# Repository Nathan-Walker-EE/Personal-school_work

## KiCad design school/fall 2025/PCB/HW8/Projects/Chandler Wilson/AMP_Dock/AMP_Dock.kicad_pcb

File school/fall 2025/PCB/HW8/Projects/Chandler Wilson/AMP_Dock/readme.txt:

Title: AMP Dock
REV: 1.0-A

Description:
The AMP Dock is a power conversion circuit that consists of two 
different buck converters that take battery inputs from a Milwaukee M18 
and a DeWalt XR. 
The system steps the voltage of these batteries down to feed a 12 V bus 
that is used to output 12 V to power a fish finder device or other similar 12 V 
powered device. The 12 V bus is also parallelly connected to a separate buck 
converter that steps down to 5V for USB-A and USB-C outputs for phone charging. 
This device will be contained in a IP67 container that has mounting points for 
the batteries and USB output ports.

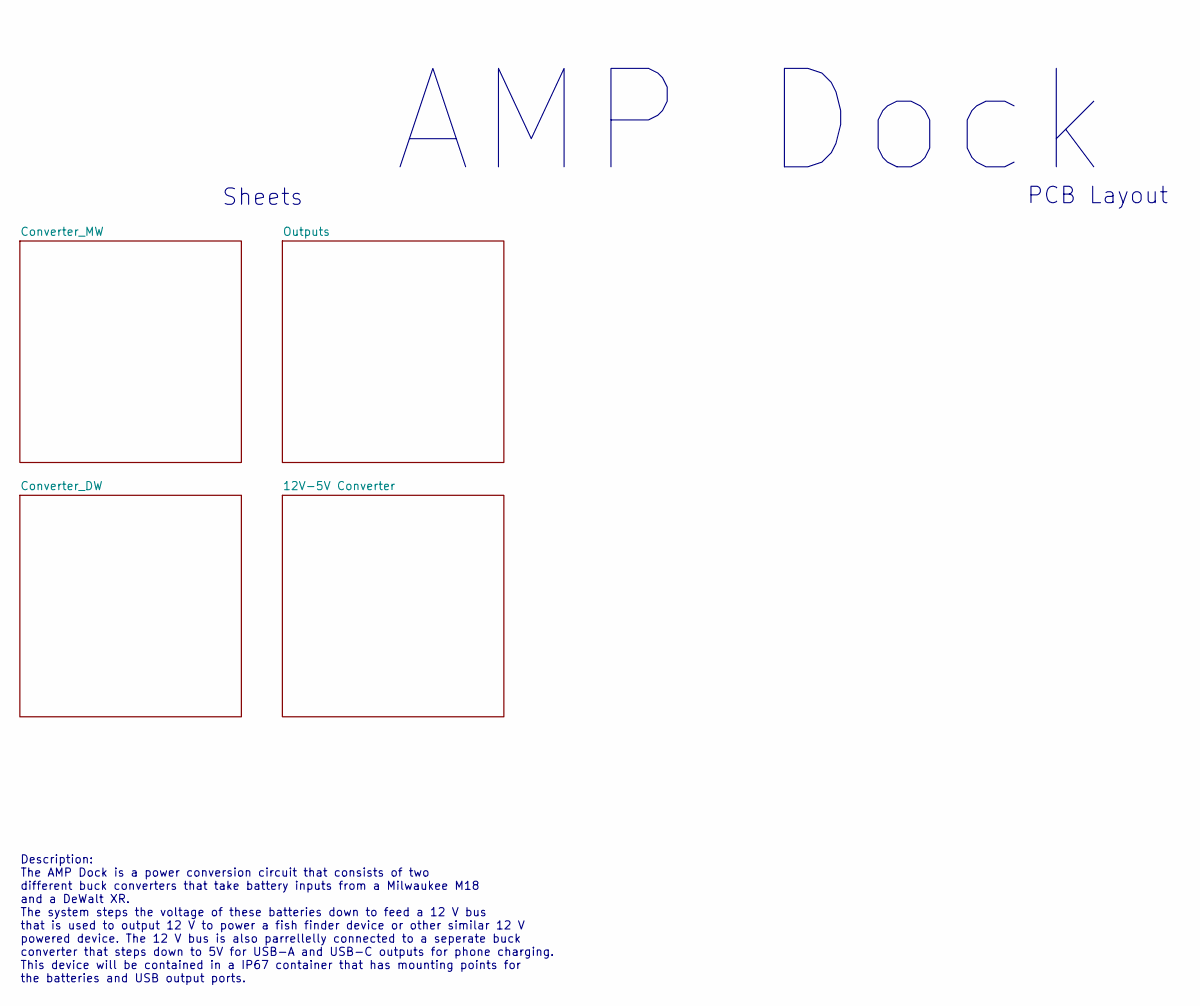
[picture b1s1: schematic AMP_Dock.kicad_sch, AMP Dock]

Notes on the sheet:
AMP Dock
Sheets
Description: The AMP Dock is a power conversion circuit that consists of two different buck converters that take battery inputs from a Milwaukee M18 and a DeWalt XR. The system steps the voltage of these batteries down to feed a 12 V bus that is used to output 12 V to power a fish finder device or 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
PCB Layout

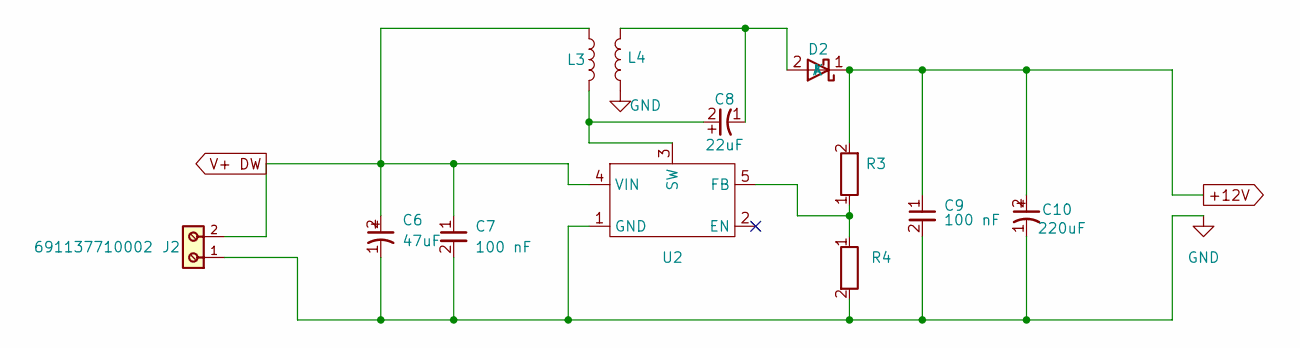
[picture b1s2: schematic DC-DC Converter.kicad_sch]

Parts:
C6: 47uF; CAP_EEFK_D_PAN
C7, C9: 100 nF; C_0805_2012Metric
C8: 22uF; CAP_6.3 X 5.8_PAN
C10: 220uF; CAP_EEFK_F_PAN
D2: DIOM7959X262N
J2: 691137710002
L3, L4: SRR1280-330M; IND_BOURNS_SRR1280
R3: R_0402_1005Metric
R4: R_0603_1608Metric
U2: XL6019

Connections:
+12V: C9.1, C10.2, D2.1 (K), R3.2; also elsewhere on the board
GND: C6.1, C7.2, C9.2, C10.1, J2.1, L4.1, R4.2, U2.1 (GND); also elsewhere on the board
unnamed: C8.1, D2.2 (A), L4.2
unnamed: R3.1, R4.1, U2.5 (FB)
unnamed: C8.2, L3.2, U2.3 (SW)
V+ DW: C6.2, C7.1, J2.2, L3.1, U2.4 (VIN)

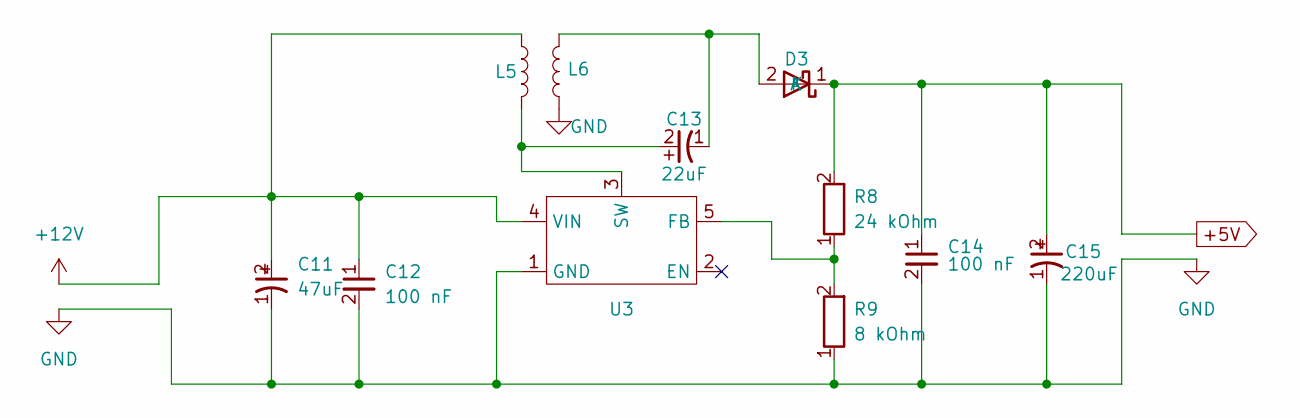
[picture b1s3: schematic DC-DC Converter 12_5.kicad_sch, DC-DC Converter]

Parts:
C11: 47uF; CAP_EEFK_D_PAN
C12, C14: 100 nF; C_0805_2012Metric
C13: 22uF; CAP_6.3 X 5.8_PAN
C15: 220uF; CAP_EEFK_F_PAN
D3: DIOM7959X262N
L5, L6: SRR1280-330M; IND_BOURNS_SRR1280
R8: 24 kOhm; R_0805_2012Metric
R9: 8 kOhm; R_0603_1608Metric
U3: XL6019

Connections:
+5V: C14.1, C15.2, D3.1 (K), R8.2; also elsewhere on the board
+12V: C11.2, C12.1, L5.1, U3.4 (VIN); also elsewhere on the board
GND: C11.1, C12.2, C14.2, C15.1, L6.1, R9.1, U3.1 (GND); also elsewhere on the board
unnamed: C13.1, D3.2 (A), L6.2
unnamed: R8.1, R9.2, U3.5 (FB)
unnamed: C13.2, L5.2, U3.3 (SW)

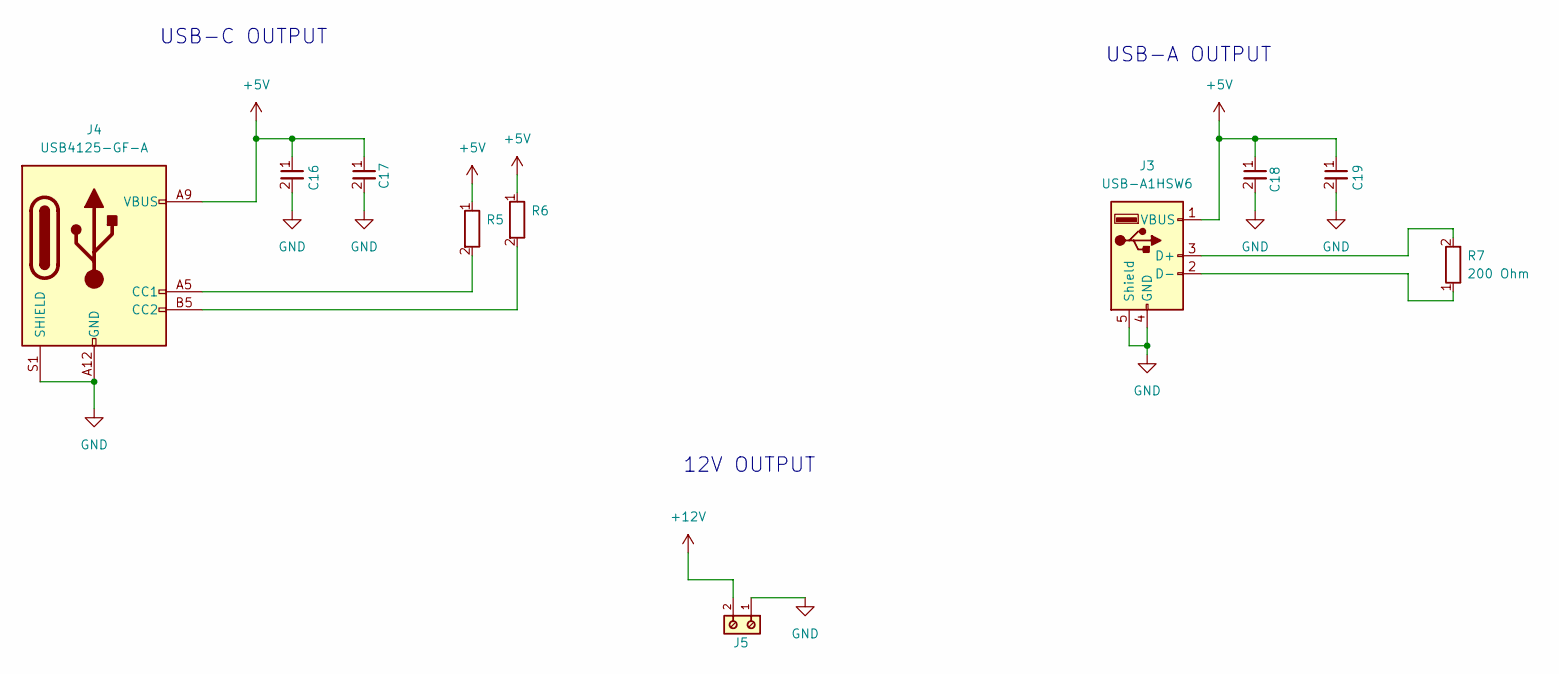
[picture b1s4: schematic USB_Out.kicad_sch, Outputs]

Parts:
C16, C17, C18, C19: 100 nF; C_0805_2012Metric
J3: USB-A1HSW6; OST_USB-A1HSW6
J4: USB4125-GF-A; GCT_USB4125-GF-A_REVA2
J5: 691137710002
R5, R6: R_0805_2012Metric
R7: 200 Ohm; R_0805_2012Metric

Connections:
+5V: C16.1, C17.1, C18.1, C19.1, J3.1 (VBUS), J4.A9 (VBUS), J4.B9 (VBUS), R5.1, R6.1; also elsewhere on the board
+12V: J5.2; also elsewhere on the board
GND: C16.2, C17.2, C18.2, C19.2, J3.4 (GND), J3.5 (Shield), J4.A12 (GND), J4.B12 (GND), J4.S1 (SHIELD), J5.1; also elsewhere on the board
unnamed: J3.3 (D+), R7.2
unnamed: J3.2 (D-), R7.1
unnamed: J4.A5 (CC1), R5.2
unnamed: J4.B5 (CC2), R6.2

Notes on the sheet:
12V OUTPUT
USB-C OUTPUT
USB-A OUTPUT

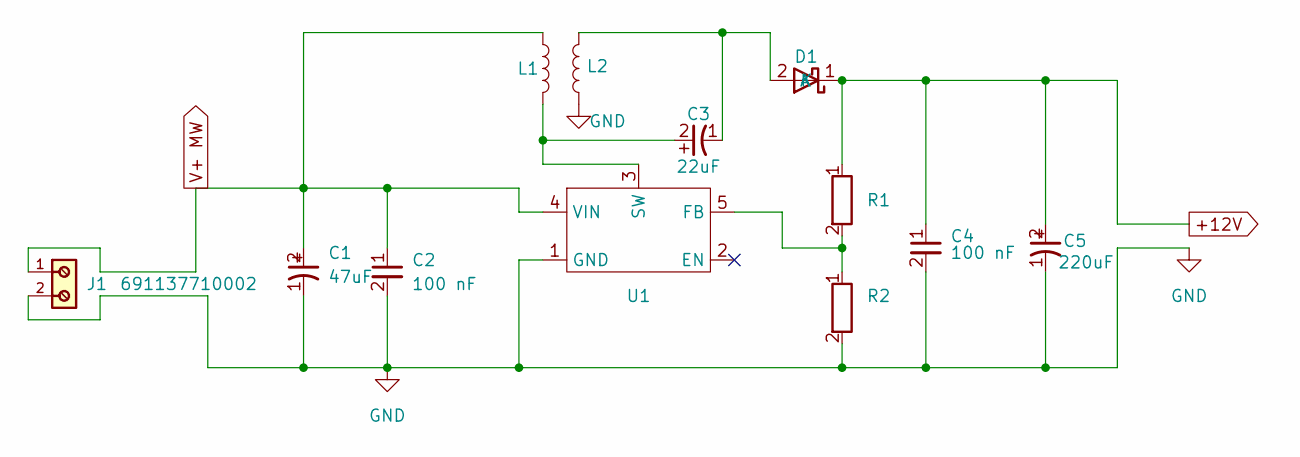
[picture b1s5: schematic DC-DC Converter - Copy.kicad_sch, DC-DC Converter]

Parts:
C1: 47uF; CAP_EEFK_D_PAN
C2, C4: 100 nF; C_0805_2012Metric
C3: 22uF; CAP_6.3 X 5.8_PAN
C5: 220uF; CAP_EEFK_F_PAN
D1: DIOM7959X262N
J1: 691137710002
L1, L2: SRR1280-330M; IND_BOURNS_SRR1280
R1: 24 kohm; R_0402_1005Metric
R2: R_0603_1608Metric
U1: XL6019

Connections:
+12V: C4.1, C5.2, D1.1 (K), R1.1; also elsewhere on the board
GND: C1.1, C2.2, C4.2, C5.1, J1.2, L2.1, R2.2, U1.1 (GND); also elsewhere on the board
unnamed: C3.1, D1.2 (A), L2.2
unnamed: R1.2, R2.1, U1.5 (FB)
unnamed: C3.2, L1.2, U1.3 (SW)
V+ MW: C1.2, C2.1, J1.1, L1.1, U1.4 (VIN)

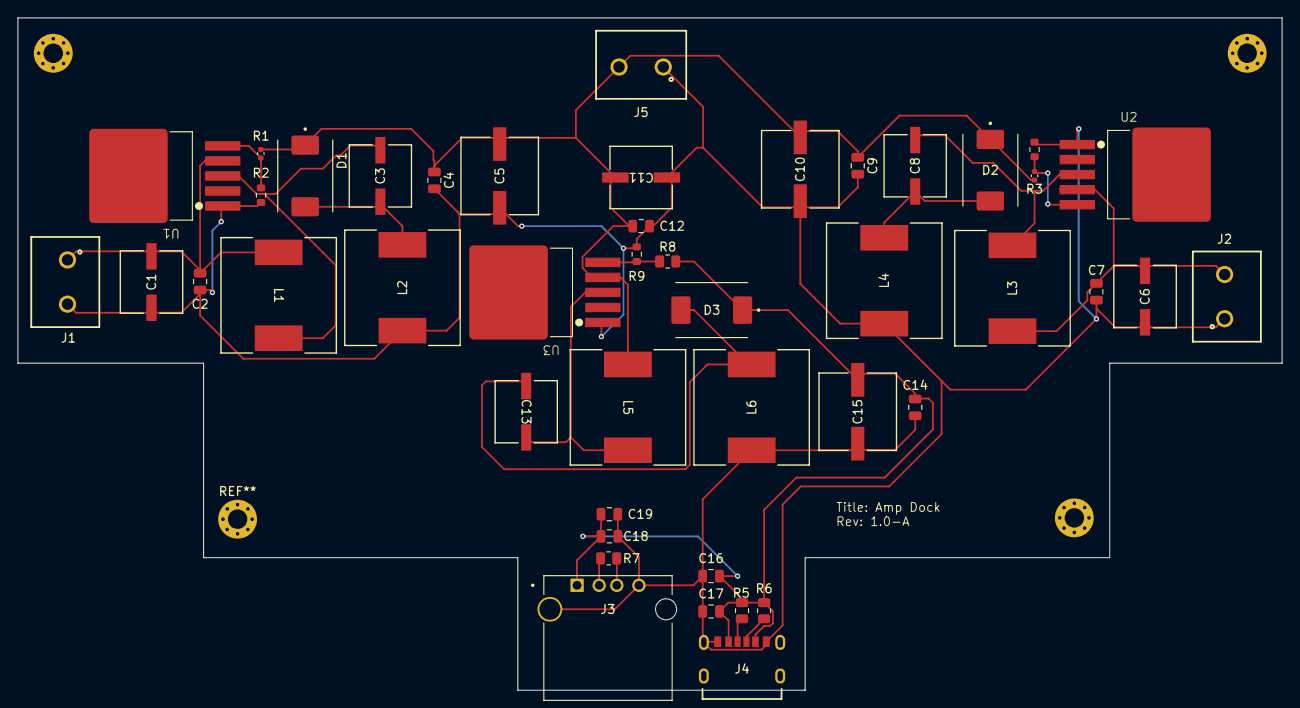
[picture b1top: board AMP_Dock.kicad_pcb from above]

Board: 2 copper layers, 143.0 x 76.1 mm, 45 parts (0 on the bottom side), 18 nets.

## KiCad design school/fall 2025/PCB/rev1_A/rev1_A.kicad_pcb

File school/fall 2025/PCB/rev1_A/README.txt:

This is Rev1_A of my PCB. It's intended purpose is to be a pmod kit
for the Basys 3 board.

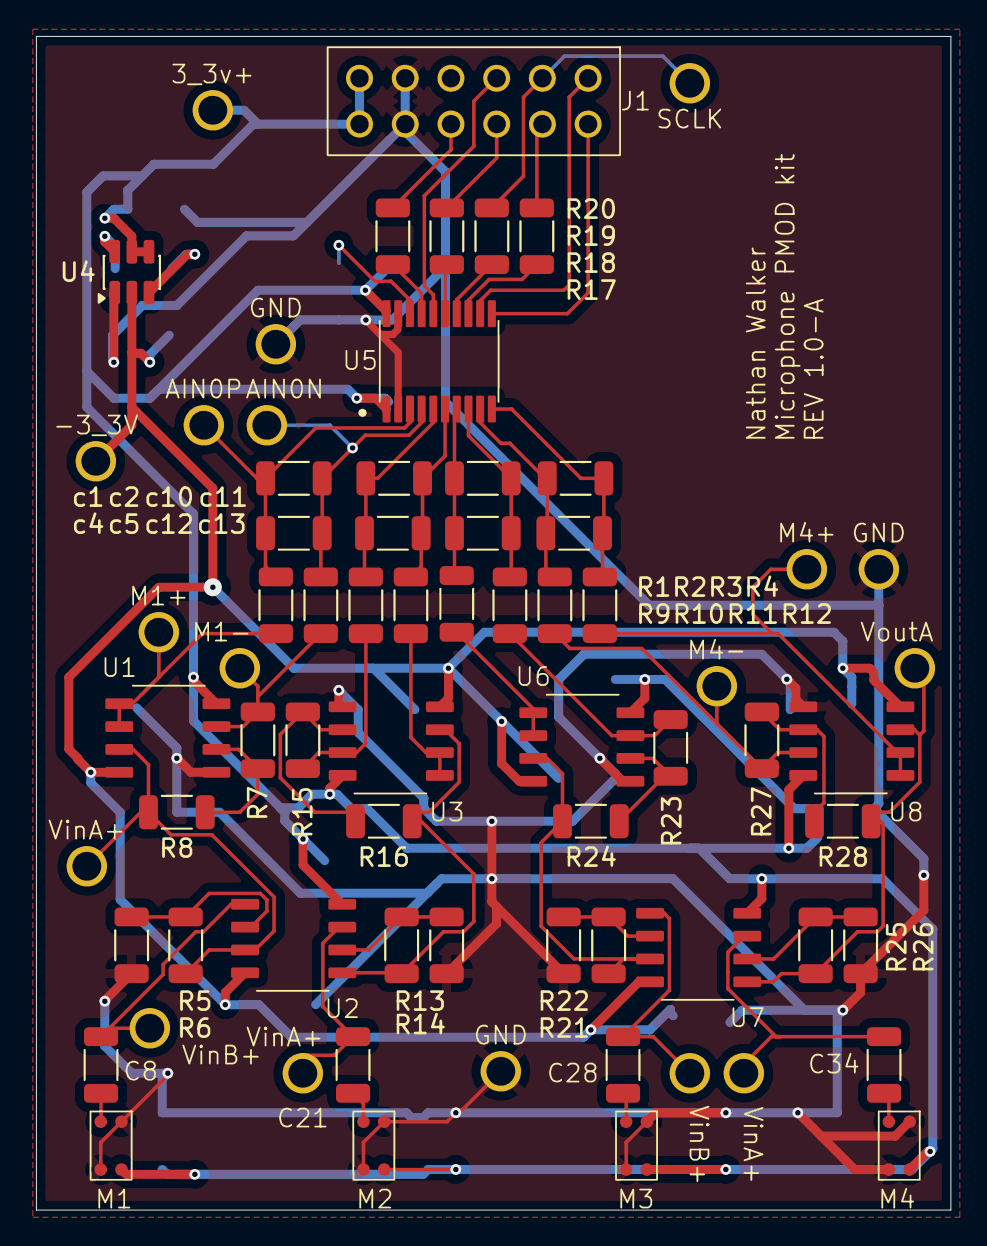
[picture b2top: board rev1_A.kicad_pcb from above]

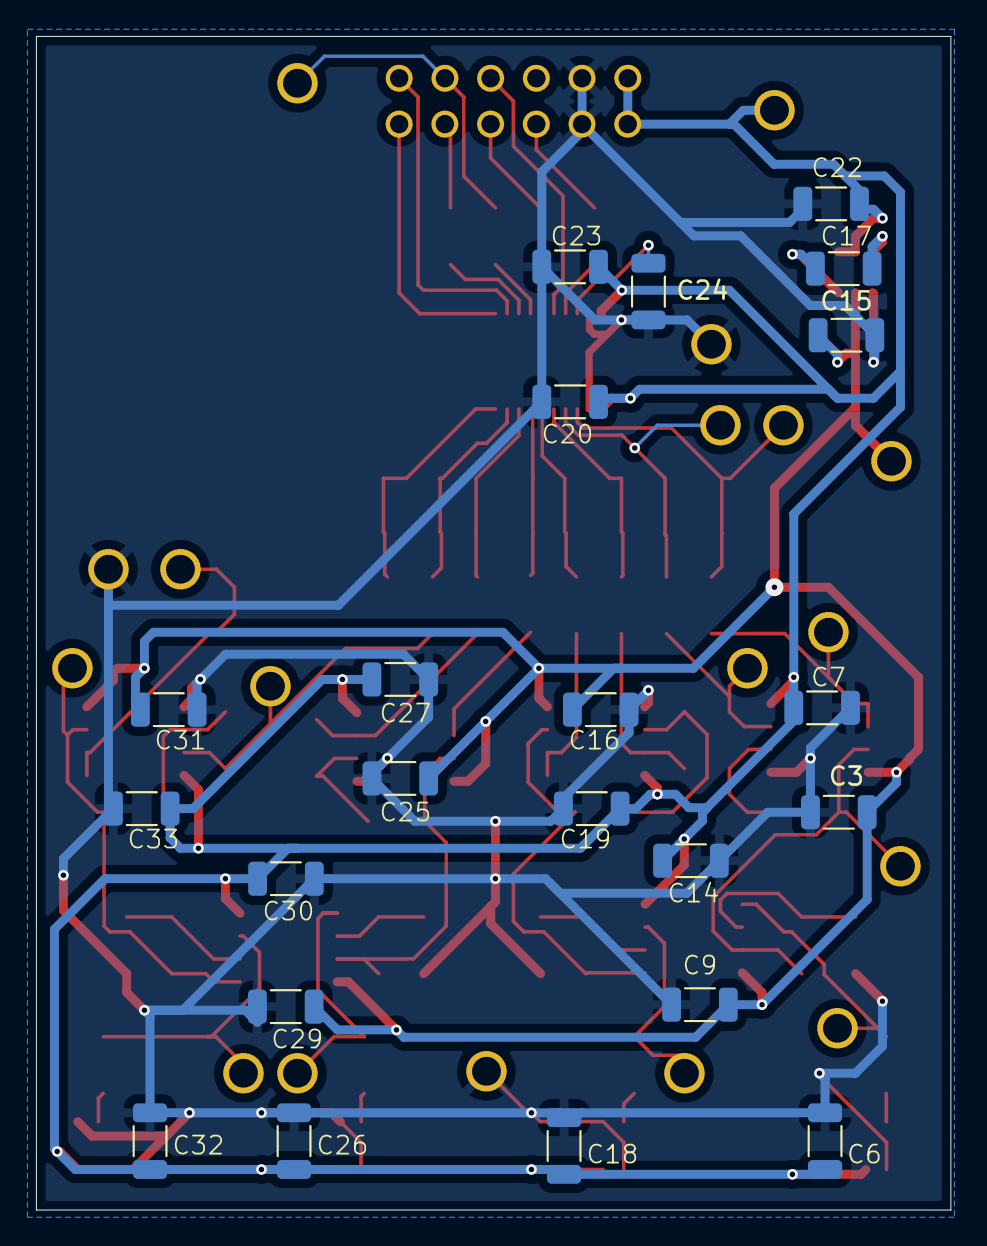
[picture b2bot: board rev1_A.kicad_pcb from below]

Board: 2 copper layers, 50.8 x 65.2 mm, 93 parts (22 on the bottom side), 53 nets.

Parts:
3_3v+: 5010
-3_3V: 5010
AIN0N, AIN0P: 5010
C3, C6, C7, C9, C14, C16, C17, C18, C19, C20, C22, C23, C25, C26, C27, C29, C30, C31, C32, C33: 1 uF; 1206 capacitor
C8, C21, C28, C34: 0.1 uF; 1206 capacitor
C15: 2.2 uF; L_1206_3216Metric
C24: 220nF; L_1206_3216Metric
GND: 5010
GND#2, GND#3: 5010
J1: PHED-RS006G1ABOGA-C006
M1, M2, M3, M4: 3SM123C4T1QA
M1+, M1-, M4+, M4-: 5010
R1, R2, R3, R4, R9, R10, R11, R12: 300; L_1206_3216Metric
R5, R14, R21, R26: 249k; L_1206_3216Metric
R6, R7, R8, R13, R15, R16, R22, R23, R24, R25, R27, R28: 10k; L_1206_3216Metric
R17, R18, R19, R20: 47; L_1206_3216Metric
SCLK: 5010
U1, U2, U3, U6, U7, U8: MCP6002
U4: SOT-23-6
U5: ADS130B02-Q1
VinA+: 5010
VinA+#2, VinA+#3: 5010
VinB+: 5010
VinB+#2: 5010
VoutA: 5010
c1, c2, c4, c5, c10, c11, c12, c13: 10nf; L_1206_3216Metric

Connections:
/3_3V+: 3_3v+.1, C6.1, C7.2, C14.1, C18.1, C19.2, C20.1, C22.1, C23.1, C26.1, C27.2, C30.1, C32.1, C33.2, J1.6 (JB6), J1.12 (JB12), M1.1 (VDD), M2.1 (VDD), M3.1 (VDD), M4.1 (VDD), U1.8 (VDD), U2.4 (VSS), U3.8 (VDD), U4.4 (SD), U4.5 (V+), U5.1 (AVDD), U5.20 (DVDD), U6.8 (VDD), U7.4 (VSS), U8.8 (VDD)
/-3_3V: -3_3V.1, C3.1, C9.2, C15.1, C16.1, C25.1, C29.2, C31.1, U1.4 (VSS), U2.8 (VDD), U3.4 (VSS), U4.2 (OUT), U6.4 (VSS), U7.8 (VDD), U8.4 (VSS)
/AIN0N: AIN0N.1, R2.1, U5.4 (AIN0N), c1.2, c4.2
/AIN0P: AIN0P.1, R1.2, U5.3 (AIN0P), c1.1, c4.1
/AIN1N: R4.1, U5.5 (AIN1N), c2.2, c5.2
/AIN1P: R3.2, U5.6 (AIN1P), c2.1, c5.1
/AIN2N: R10.1, U5.8 (AIN2N), c10.2, c12.2
/AIN2P: R9.2, U5.7 (AIN2P), c10.1, c12.1
/AIN3N: R12.1, U5.9 (AIN3N), c11.2, c13.2
/AIN3P: R11.2, U5.10 (AIN3P), c11.1, c13.1
/CLKIN: J1.4 (JB4), R17.2
/CS_: J1.7 (JB7), U5.12 (CS_)
/DIN: J1.9 (JB9), U5.16 (DIN)
/DOUT: J1.3 (JB3), R18.2
/DRDY_: J1.2 (JB2), R20.2
/M1+: M1+.1, R1.1, U1.1 (VoutA), U1.2 (VinA-)
/M1-: M1-.1, R2.2, R7.2, U1.7 (VoutB)
/M1_amplified: R6.2, R8.1, U1.3 (VinA+), U2.7 (VoutB)
/M2+: R3.1, U3.1 (VoutA), U3.2 (VinA-)
/M2-: R4.2, R15.2, U3.7 (VoutB)
/M2_amplified: R13.2, R16.2, U2.1 (VoutA), U3.3 (VinA+)
/M3+: R9.1, U6.1 (VoutA), U6.2 (VinA-)
/M3-: R10.2, R23.2, U6.7 (VoutB)
/M3_amplified: R22.2, R24.1, U6.3 (VinA+), U7.7 (VoutB)
/M4+: M4+.1, R11.1, U8.1 (VoutA), U8.2 (VinA-)
/M4-: M4-.1, R12.2, R27.2, U8.7 (VoutB)
/M4_amplified: R25.2, R28.2, U7.1 (VoutA), U8.3 (VinA+)
/SCLK: J1.8 (JB8), R19.2, SCLK.1
/SYNC_: J1.1 (JB1), U5.11 (SYNC_)
/VinA+_M2: C21.2, U2.3 (VinA+)
/VinA+_M4: C34.2, U7.3 (VinA+)
/VinB+_M1: C8.2, U2.5 (VinB+)
/VinB+_M3: C28.2, U7.5 (VinB+)
GND: C3.2, C6.2, C7.1, C9.1, C14.2, C15.2, C16.2, C18.2, C19.1, C20.2, C22.2, C23.2, C24.2, C25.2, C26.2, C27.1, C29.1, C30.2, C31.2, C32.2, C33.1, GND.1, GND#2.1, GND#3.1, J1.5 (JB5), J1.11 (JB11), M1.2 (GND), M1.3 (GND), M2.2 (GND), M2.3 (GND), M3.2 (GND), M3.3 (GND), M4.2 (GND), M4.3 (GND), R5.2, R14.1, R21.2, R26.1, U1.5 (VinB+), U3.5 (VinB+), U4.1 (GND), U5.2 (AGND), U5.19 (DGND), U6.5 (VinB+), U8.5 (VinB+)
unnamed: C8.1, M1.4 (OUT)
unnamed: C21.1, M2.4 (OUT)
unnamed: C28.1, M3.4 (OUT)
unnamed: C34.1, M4.4 (OUT)
unnamed: R7.1, R8.2, U1.6 (VinB-)
unnamed: R13.1, R14.2, U2.2 (VinA-)
unnamed: R5.1, R6.1, U2.6 (VinB-)
unnamed: R15.1, R16.1, U3.6 (VinB-)
unnamed: C17.2, U4.6 (CAP+)
unnamed: C17.1, U4.3 (CAP-)
unnamed: C24.1, U5.18 (CAP)
unnamed: R17.1, U5.17 (CLKIN)
unnamed: R18.1, U5.15 (DOUT)
unnamed: R20.1, U5.13 (DRDY_)
unnamed: R19.1, U5.14 (SCLK)
unnamed: R23.1, R24.2, U6.6 (VinB-)
unnamed: R25.1, R26.2, U7.2 (VinA-)
unnamed: R21.1, R22.1, U7.6 (VinB-)
unnamed: R27.1, R28.1, U8.6 (VinB-)

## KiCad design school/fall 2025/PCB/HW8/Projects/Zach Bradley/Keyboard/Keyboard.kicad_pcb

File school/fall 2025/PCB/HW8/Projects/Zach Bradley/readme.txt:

Intention: Build a Split Keyboard PCB
The circuit uses switches, diodes, resistors, capacitors, MCUs, and a crystal oscillator.
The project is not quite complete, and needs a second revision to work, details below.
Another intention is to learn KiCad to progress in PCB design.

Scope: This board scans a keyboard matrix and properly relays the correct switch pressed to the PC.
The scope of this project is to anyone who needs a split keyboard for carpal tunnel protection, PCB design experience, or customization of a keyboard/PCB.

Function: Demonstrates an understanding of KiCad software and preventative measures for carpal tunnel.

IGNORED ERRORS:
None in the ERC.

Errors in the PCB include not finished routing all the necessary traces.
I have to think through the design just a bit more to ensure that I can properly separate the two sides, program the MCU properly, and route all the traces.

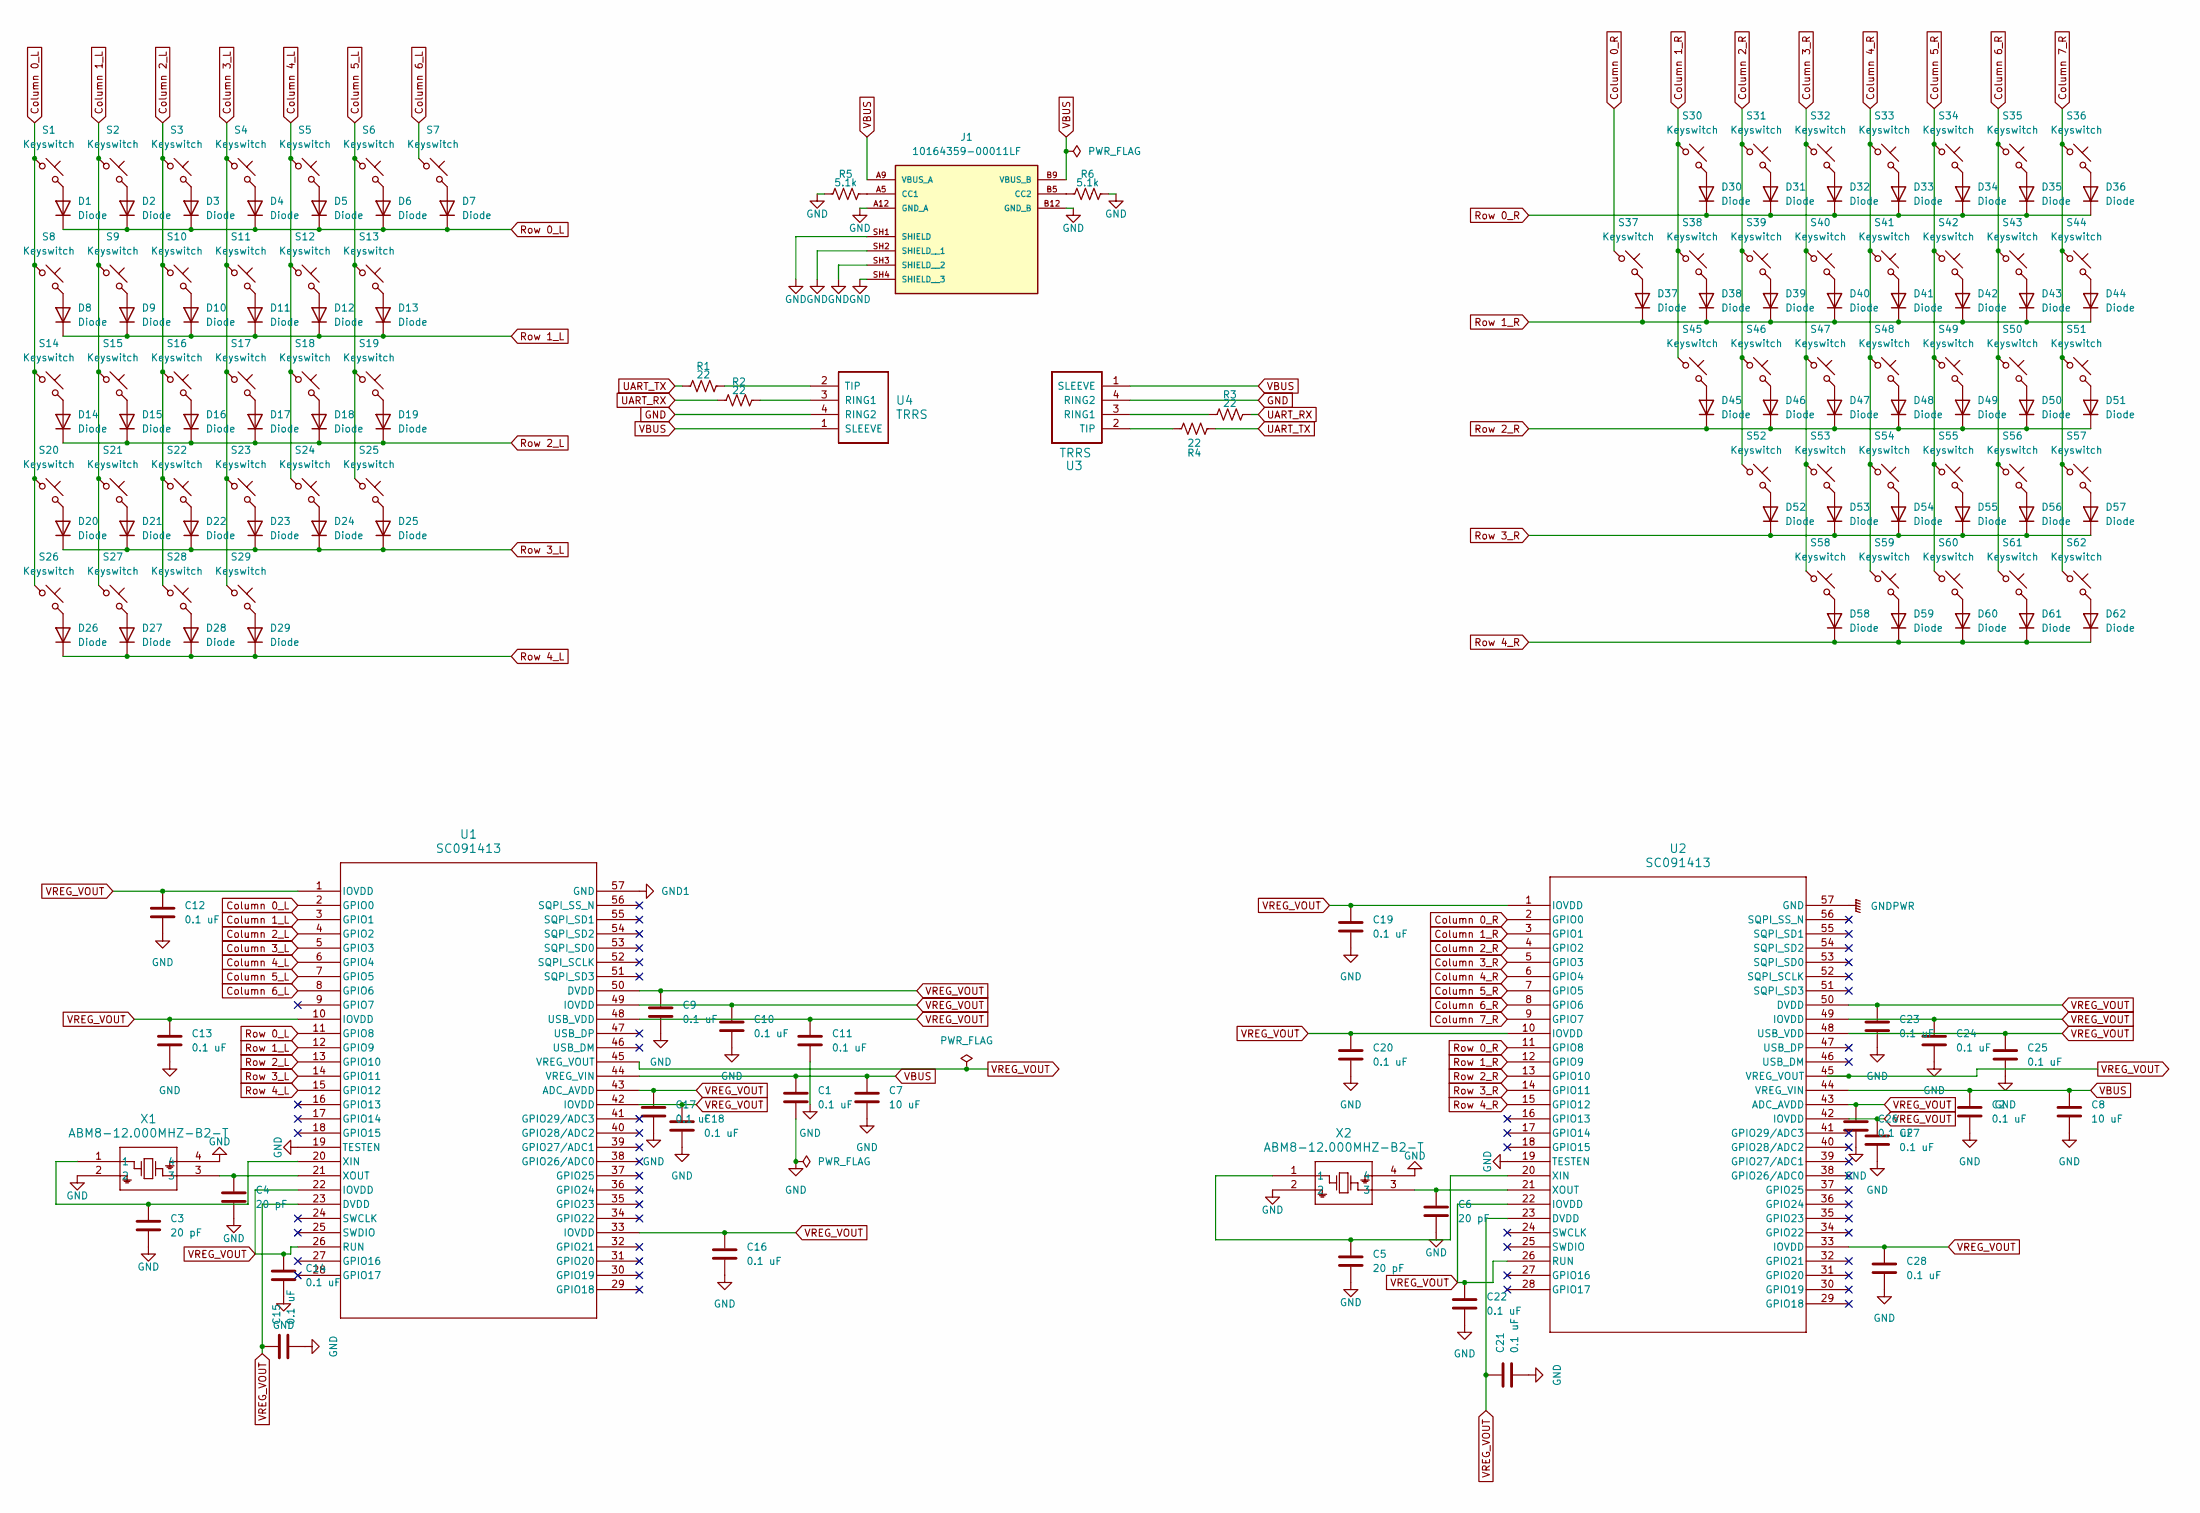
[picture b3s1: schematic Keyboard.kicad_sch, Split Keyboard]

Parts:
C1, C2, C9, C10, C11, C12, C13, C14, C15, C16, C17, C18, C19, C20, C21, C22, C23, C24, C25, C26, C27, C28: 0.1 uF; 0603_AVX
C3, C4, C5, C6: 20 pF; CAP_CC0201_YAG
C7, C8: 10 uF; CAPC345180_180N_KEM
D1, D2, D3, D4, D5, D6, D7, D8, D9, D10, D11, D12, D13, D14, D15, D16, D17, D18, D19, D20, D21, D22, D23, D24, D25, D26, D27, D28, D29, D30, D31, D32, D33, D34, D35, D36, D37, D38, D39, D40, D41, D42, D43, D44, D45, D46, D47, D48, D49, D50, D51, D52, D53, D54, D55, D56, D57, D58, D59, D60, D61, D62: Diode; Diode_DO-35
J1: 10164359-00011LF; AMPHENOL_10164359-00011LF; PARTREV A
R1, R2, R3, R4: 22; RC0402N_YAG
R5, R6: 5.1k; RC0603N_YAG
S1, S2, S3, S4, S5, S6, S7, S9, S10, S11, S12, S13, S15, S16, S17, S18, S19, S21, S22, S23, S24, S25, S30, S31, S32, S33, S34, S35, S37, S38, S39, S40, S41, S42, S43, S45, S46, S47, S48, S49, S50, S52, S53, S54, S55, S56, S57, S60, S61, S62: Keyswitch; Hotswap_MX_Plated_1.00u
S8, S44: Keyswitch; Hotswap_MX_Plated_1.50u
S14: Keyswitch; Hotswap_MX_Plated_1.75u
S20, S36: Keyswitch; Hotswap_MX_Plated_2.00u
S26, S27, S28, S59: Keyswitch; Hotswap_MX_Plated_1.25u
S29, S58: Keyswitch; Hotswap_MX_Plated_5.50u
S51: Keyswitch; Hotswap_MX_Plated_2.25u
U1, U2: SC091413; QFN56_7X7_RPI
U3, U4: TRRS; TRRS_PJ-320A
X1, X2: ABM8-12.000MHZ-B2-T; ABM8_ABR

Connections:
Column 0_L: S1.1, S8.1, S14.1, S20.1, S26.1, U1.2 (GPIO0)
Column 0_R: S37.1, U2.2 (GPIO0)
Column 1_L: S2.1, S9.1, S15.1, S21.1, S27.1, U1.3 (GPIO1)
Column 1_R: S30.1, S38.1, S45.1, U2.3 (GPIO1)
Column 2_L: S3.1, S10.1, S16.1, S22.1, S28.1, U1.4 (GPIO2)
Column 2_R: S31.1, S39.1, S46.1, S52.1, U2.4 (GPIO2)
Column 3_L: S4.1, S11.1, S17.1, S23.1, S29.1, U1.5 (GPIO3)
Column 3_R: S32.1, S40.1, S47.1, S53.1, S58.1, U2.5 (GPIO3)
Column 4_L: S5.1, S12.1, S18.1, S24.1, U1.6 (GPIO4)
Column 4_R: S33.1, S41.1, S48.1, S54.1, S59.1, U2.6 (GPIO4)
Column 5_L: S6.1, S13.1, S19.1, S25.1, U1.7 (GPIO5)
Column 5_R: S34.1, S42.1, S49.1, S55.1, S60.1, U2.7 (GPIO5)
Column 6_L: S7.1, U1.8 (GPIO6)
Column 6_R: S35.1, S43.1, S50.1, S56.1, S61.1, U2.8 (GPIO6)
Column 7_R: S36.1, S44.1, S51.1, S57.1, S62.1, U2.9 (GPIO7)
GND: C1.2, C2.2, C3.2, C4.2, C5.2, C6.2, C7.2, C8.2, C9.2, C10.2, C11.2, C12.2, C13.2, C14.2, C15.2, C16.2, C17.2, C18.2, C19.2, C20.2, C21.2, C22.2, C23.2, C24.2, C25.2, C26.2, C27.2, C28.2, J1.A12 (GND_A), J1.B12 (GND_B), J1.SH1 (SHIELD), J1.SH2 (SHIELD__1), J1.SH3 (SHIELD__2), J1.SH4 (SHIELD__3), R5.1, R6.2, U1.19 (TESTEN), U2.19 (TESTEN), U3.4 (RING2), U4.4 (RING2), X1.2, X1.4, X2.2, X2.4
unnamed: D1.2 (A), S1.2
unnamed: D2.2 (A), S2.2
unnamed: D3.2 (A), S3.2
unnamed: D4.2 (A), S4.2
unnamed: D5.2 (A), S5.2
unnamed: D6.2 (A), S6.2
unnamed: D7.2 (A), S7.2
unnamed: D8.2 (A), S8.2
unnamed: D9.2 (A), S9.2
unnamed: D10.2 (A), S10.2
unnamed: D11.2 (A), S11.2
unnamed: D12.2 (A), S12.2
unnamed: D13.2 (A), S13.2
unnamed: D14.2 (A), S14.2
unnamed: D15.2 (A), S15.2
unnamed: D16.2 (A), S16.2
unnamed: D17.2 (A), S17.2
unnamed: D18.2 (A), S18.2
unnamed: D19.2 (A), S19.2
unnamed: D20.2 (A), S20.2
unnamed: D21.2 (A), S21.2
unnamed: D22.2 (A), S22.2
unnamed: D23.2 (A), S23.2
unnamed: D24.2 (A), S24.2
unnamed: D25.2 (A), S25.2
unnamed: D26.2 (A), S26.2
unnamed: D27.2 (A), S27.2
unnamed: D28.2 (A), S28.2
unnamed: D29.2 (A), S29.2
unnamed: D30.2 (A), S30.2
unnamed: D31.2 (A), S31.2
unnamed: D32.2 (A), S32.2
unnamed: D33.2 (A), S33.2
unnamed: D34.2 (A), S34.2
unnamed: D35.2 (A), S35.2
unnamed: D36.2 (A), S36.2
unnamed: D37.2 (A), S37.2
unnamed: D38.2 (A), S38.2
unnamed: D39.2 (A), S39.2
unnamed: D40.2 (A), S40.2
unnamed: D41.2 (A), S41.2
unnamed: D42.2 (A), S42.2
unnamed: D43.2 (A), S43.2
unnamed: D44.2 (A), S44.2
unnamed: D45.2 (A), S45.2
unnamed: D46.2 (A), S46.2
unnamed: D47.2 (A), S47.2
unnamed: D48.2 (A), S48.2
unnamed: D49.2 (A), S49.2
unnamed: D50.2 (A), S50.2
unnamed: D51.2 (A), S51.2
unnamed: D52.2 (A), S52.2
unnamed: D53.2 (A), S53.2
unnamed: D54.2 (A), S54.2
unnamed: D55.2 (A), S55.2
unnamed: D56.2 (A), S56.2
unnamed: D57.2 (A), S57.2
unnamed: D58.2 (A), S58.2
unnamed: D59.2 (A), S59.2
unnamed: D60.2 (A), S60.2
unnamed: D61.2 (A), S61.2
unnamed: D62.2 (A), S62.2
unnamed: J1.A5 (CC1), R5.2
unnamed: J1.B5 (CC2), R6.1
unnamed: C3.1, U1.20 (XIN), X1.1
unnamed: C4.1, U1.21 (XOUT), X1.3
unnamed: C5.1, U2.20 (XIN), X2.1
unnamed: C6.1, U2.21 (XOUT), X2.3
unnamed: R3.1, U3.3 (RING1)
unnamed: R4.1, U3.2 (TIP)
unnamed: R2.2, U4.3 (RING1)
unnamed: R1.2, U4.2 (TIP)
Row 0_L: D1.1 (K), D2.1 (K), D3.1 (K), D4.1 (K), D5.1 (K), D6.1 (K), D7.1 (K), U1.11 (GPIO8)
Row 0_R: D30.1 (K), D31.1 (K), D32.1 (K), D33.1 (K), D34.1 (K), D35.1 (K), D36.1 (K), U2.11 (GPIO8)
Row 1_L: D8.1 (K), D9.1 (K), D10.1 (K), D11.1 (K), D12.1 (K), D13.1 (K), U1.12 (GPIO9)
Row 1_R: D37.1 (K), D38.1 (K), D39.1 (K), D40.1 (K), D41.1 (K), D42.1 (K), D43.1 (K), D44.1 (K), U2.12 (GPIO9)
Row 2_L: D14.1 (K), D15.1 (K), D16.1 (K), D17.1 (K), D18.1 (K), D19.1 (K), U1.13 (GPIO10)
Row 2_R: D45.1 (K), D46.1 (K), D47.1 (K), D48.1 (K), D49.1 (K), D50.1 (K), D51.1 (K), U2.13 (GPIO10)
Row 3_L: D20.1 (K), D21.1 (K), D22.1 (K), D23.1 (K), D24.1 (K), D25.1 (K), U1.14 (GPIO11)
Row 3_R: D52.1 (K), D53.1 (K), D54.1 (K), D55.1 (K), D56.1 (K), D57.1 (K), U2.14 (GPIO11)
Row 4_L: D26.1 (K), D27.1 (K), D28.1 (K), D29.1 (K), U1.15 (GPIO12)
Row 4_R: D58.1 (K), D59.1 (K), D60.1 (K), D61.1 (K), D62.1 (K), U2.15 (GPIO12)
UART_RX: R2.1, R3.2
UART_TX: R1.1, R4.2
VBUS: C1.1, C2.1, C7.1, C8.1, J1.A9 (VBUS_A), J1.B9 (VBUS_B), U1.44 (VREG_VIN), U2.44 (VREG_VIN), U3.1 (SLEEVE), U4.1 (SLEEVE)
VREG_VOUT: C9.1, C10.1, C11.1, C12.1, C13.1, C14.1, C15.1, C16.1, C17.1, C18.1, C19.1, C20.1, C21.1, C22.1, C23.1, C24.1, C25.1, C26.1, C27.1, C28.1, U1.1 (IOVDD), U1.10 (IOVDD), U1.22 (IOVDD), U1.23 (DVDD), U1.26 (RUN), U1.33 (IOVDD), U1.42 (IOVDD), U1.43 (ADC_AVDD), U1.45 (VREG_VOUT), U1.48 (USB_VDD), U1.49 (IOVDD), U1.50 (DVDD), U2.1 (IOVDD), U2.10 (IOVDD), U2.22 (IOVDD), U2.23 (DVDD), U2.26 (RUN), U2.33 (IOVDD), U2.42 (IOVDD), U2.43 (ADC_AVDD), U2.45 (VREG_VOUT), U2.48 (USB_VDD), U2.49 (IOVDD), U2.50 (DVDD)

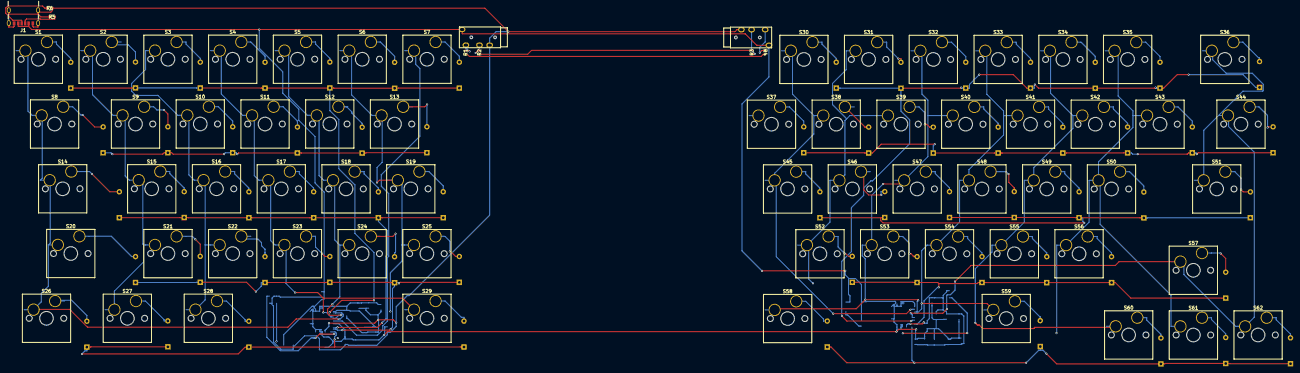
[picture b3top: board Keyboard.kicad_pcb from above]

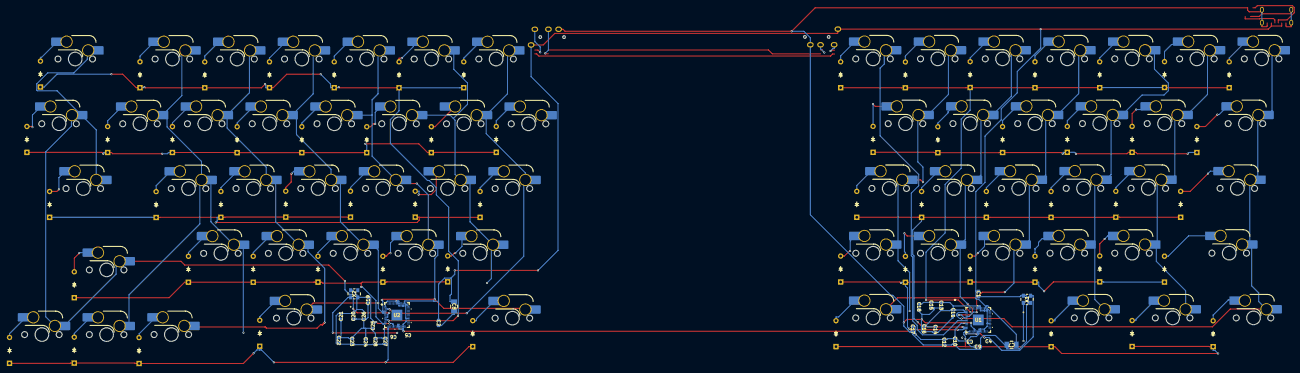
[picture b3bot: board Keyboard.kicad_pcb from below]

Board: 2 copper layers, 165 parts (94 on the bottom side), 102 nets.
